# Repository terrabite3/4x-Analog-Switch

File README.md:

# 4x Analog Switch

This is a quad analog switch based on the [MAX333A](https://datasheets.maximintegrated.com/en/ds/MAX333A.pdf) analog switch IC. The jacks are *directly* connected to the switch IC for minimum resistance and maximum versatility. 

The switch may be used in either direction.

* Send two signals into the `A` and `B` ports, and select which one goes to the `X` port.
* Send a signal into the `X` port, and select whether it goes to the `A` or `B` port. The other port is pulled low with a 100k resistor.

The connection is selected by both the toggle switch and the `SEL` input. The toggle is a 3-position switch.

* When the switch is in the up position, `A` is selected.
* When the switch is in the down position, `B` is selected.
* When the switch is in the middle position, the `SEL` input selects `A` or `B`.
* If `SEL` is high (above 3V), `A` is selected. If `SEL` is low (below 2V), `B` is selected. The `SEL` input has a Schmitt trigger so that slowly changing inputs won't cause glitches.
* If the `SEL` input is unconnected and the switch is in the middle position, `B` is selected by default.

In addition to the standard 10-pin Eurorack power header, I've included two daisy-chain power headers at the top corners of the board. This will allow adjacent units to share power. I plan to add these to most of my new designs.

## BOM

Please see the [interactive BOM](https://htmlpreview.github.io/?https://github.com/terrabite3/4x-Analog-Switch/blob/main/bom/ibom.html) for full details. Most of the parts are super common and any established maker will have them in stock. The exception is the MAX333A itself, which is rather expensive -- $16 each at this time. I only used it because I already had them in my stash!

Note that the toggle switches must be SPDT **ON-OFF-ON** configuration!

### MAX4533 substitution

After designing this module, I learned of the [MAX4533](https://datasheets.maximintegrated.com/en/ds/MAX4533.pdf), which is pin compatible with the MAX333A. It features fault protection and is actually $4 cheaper at this writing. The only downside I see is somewhat higher on resistance. I recommend that you use this part instead.

## License

* You are free to build this design, modify it, and use parts of it in other designs.
* Most PCB fabs have a minimum order of 5 units. You may sell excess PCBs as bare PCBs, kits, or fully assembled modules. Just don't order extras with the intent of selling them.
* If you make substantial changes to the design, then you may treat the design as your own. For example, adding features, removing features, or changing the form factor. Changing the font on the panel and other superficial changes would not count.
* I urge you to release any derivative works under similar terms, but you don't have to.

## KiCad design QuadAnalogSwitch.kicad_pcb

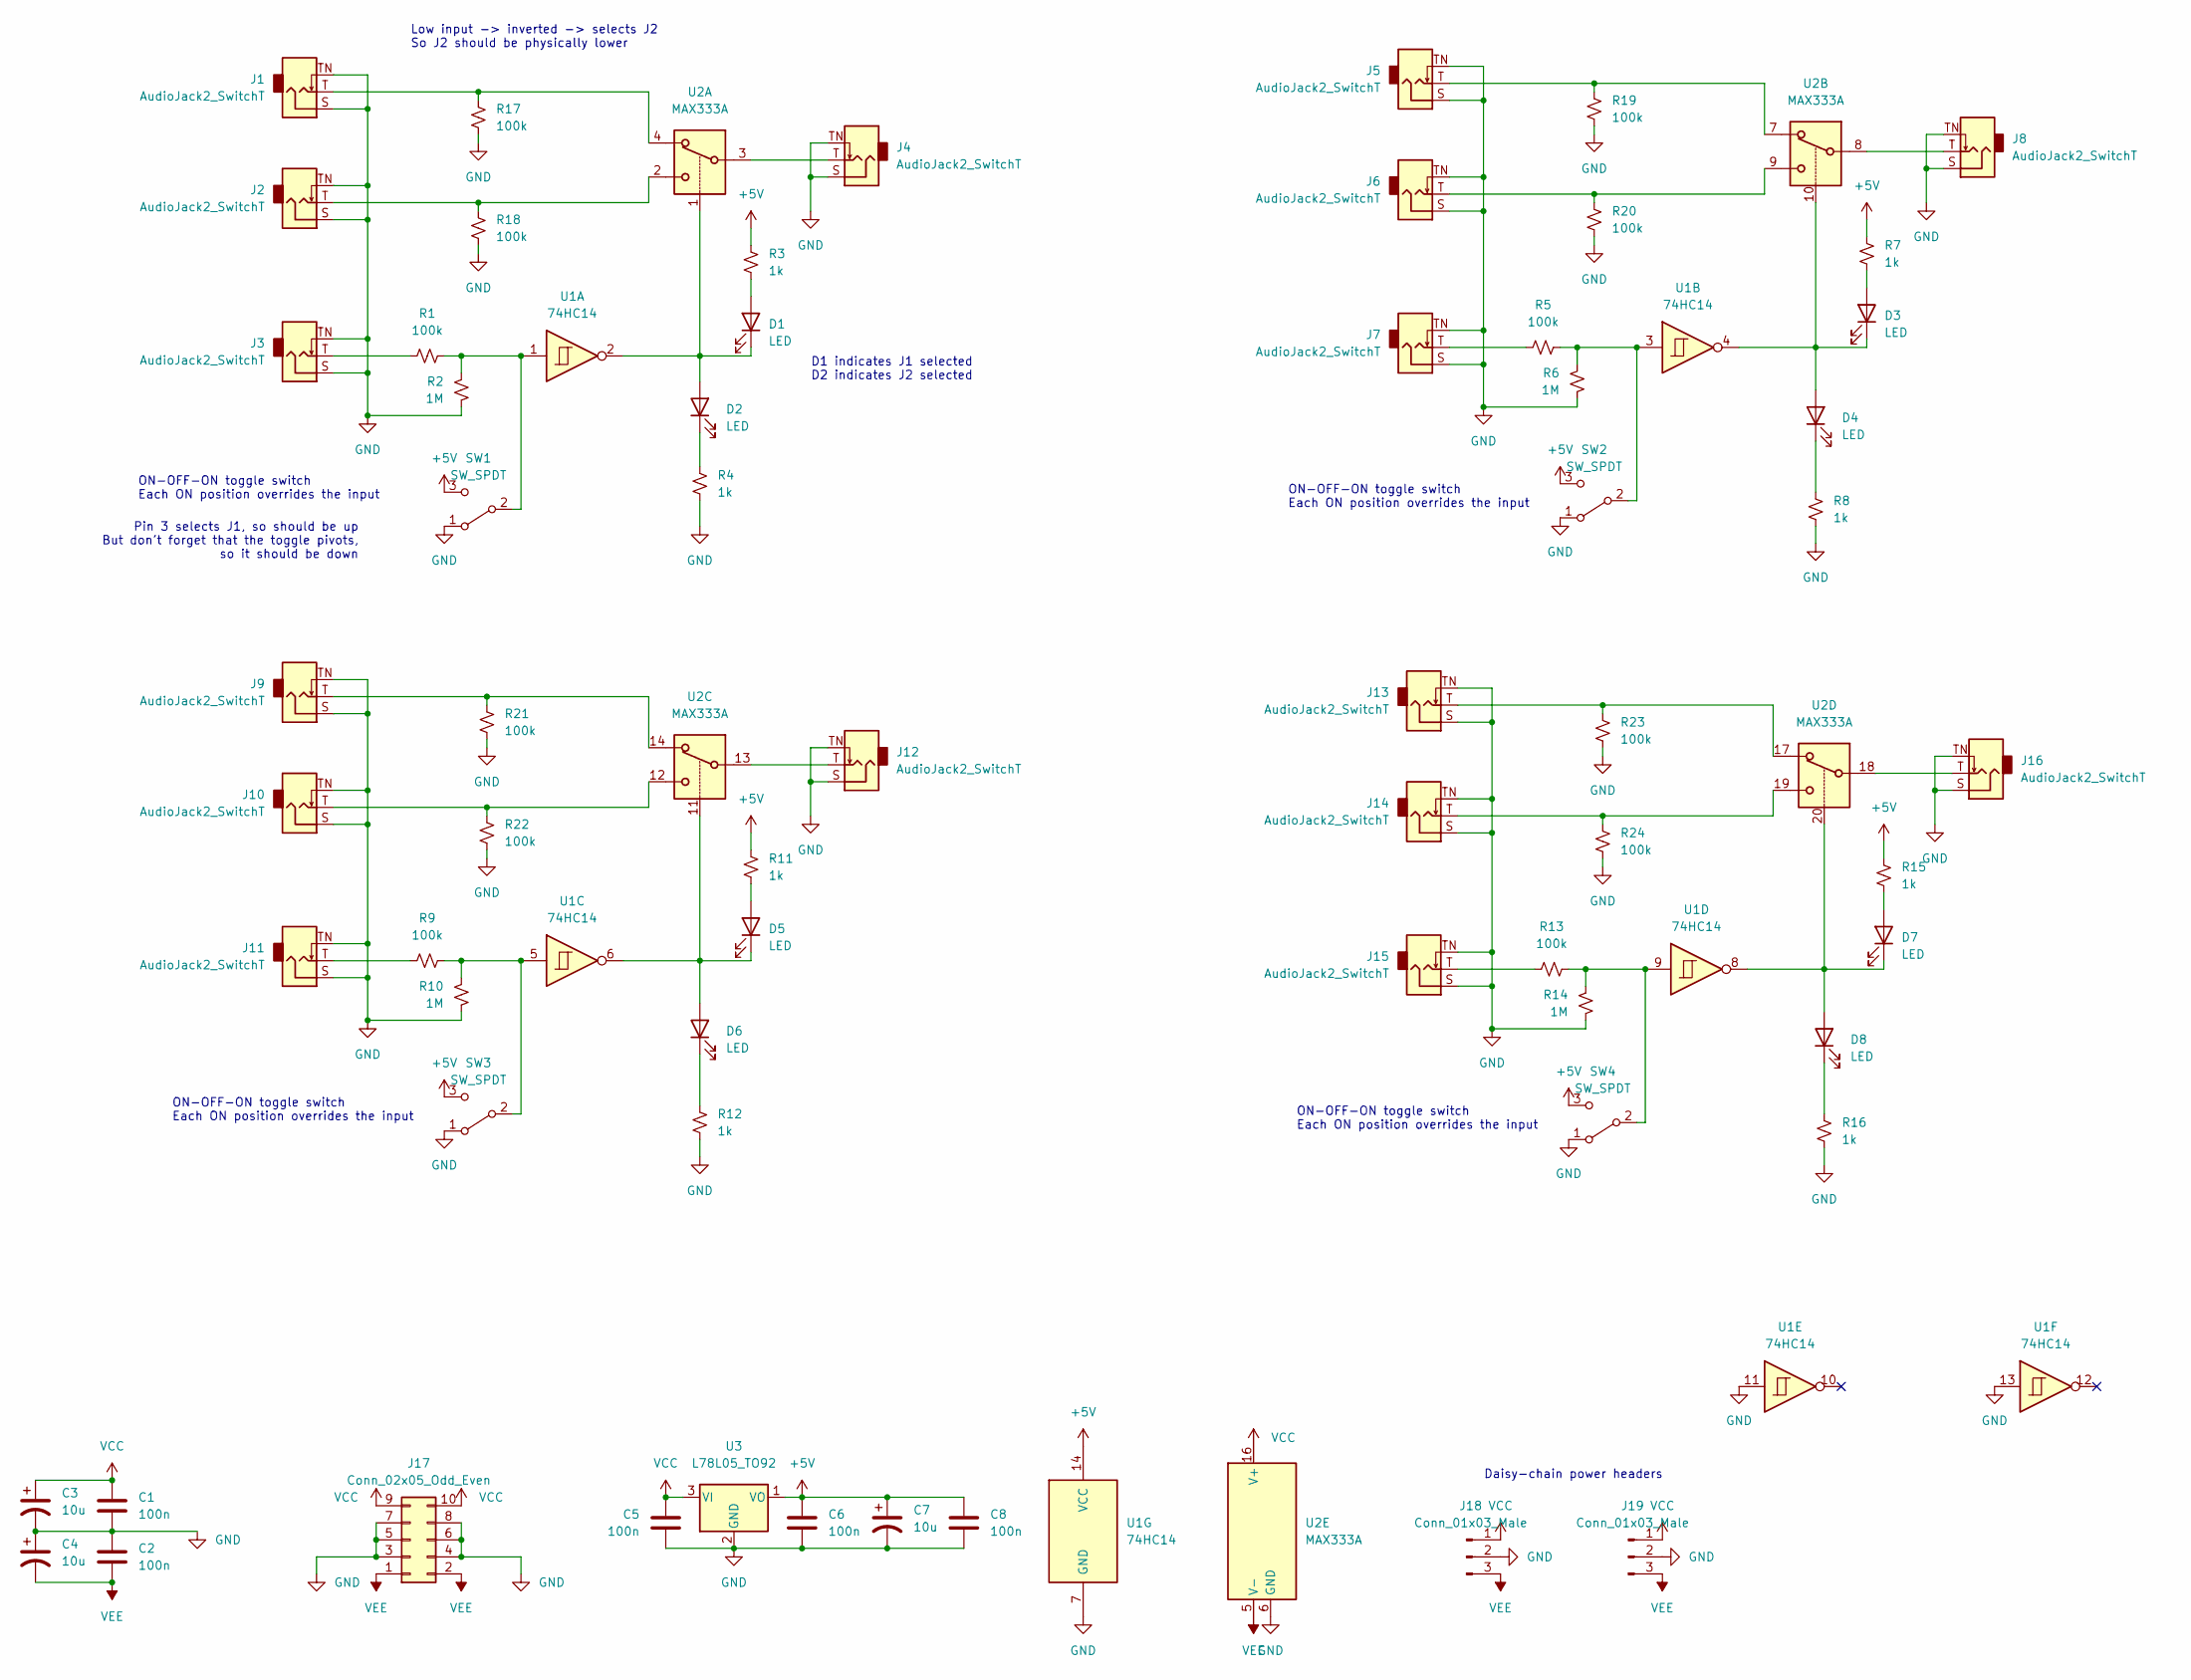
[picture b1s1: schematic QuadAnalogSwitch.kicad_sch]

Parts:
C1, C2, C5, C6, C8: 100n; C_Disc_D3.0mm_W1.6mm_P2.50mm
C3, C4, C7: 10u; CP_Radial_D5.0mm_P2.50mm
D1, D2, D3, D4, D5, D6, D7, D8: LED; LED_D3.0mm
J1, J2, J3, J4, J5, J6, J7, J8, J9, J10, J11, J12, J13, J14, J15, J16: AudioJack2_SwitchT; Jack_3.5mm_QingPu_WQP-PJ398SM_Stefan
J17: Conn_02x05_Odd_Even; IDC-Header_2x05_P2.54mm_Vertical
J18, J19: Conn_01x03_Male; PinHeader_1x03_P2.54mm_Vertical
R1, R5, R9, R13, R17, R18, R19, R20, R21, R22, R23, R24: 100k; R_Axial_DIN0204_L3.6mm_D1.6mm_P7.62mm_Horizontal
R2, R6, R10, R14: 1M; R_Axial_DIN0204_L3.6mm_D1.6mm_P7.62mm_Horizontal
R3, R4, R7, R8, R11, R12, R15, R16: 1k; R_Axial_DIN0204_L3.6mm_D1.6mm_P7.62mm_Horizontal
SW1, SW2, SW3, SW4: SW_SPDT; SW_MINI_TOGGLE
U1: 74HC14; DIP-14_W7.62mm
U2: MAX333A; DIP-20_W7.62mm
U3: L78L05_TO92; TO-92L_Inline_Wide

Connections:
+5V: C6.2, C7.1, C8.2, R3.2, R7.2, R11.2, R15.2, SW1.3 (C), SW2.3 (C), SW3.3 (C), SW4.3 (C), U1.14 (VCC), U3.1 (VO)
GND: C1.1, C2.2, C3.2, C4.1, C5.1, C6.1, C7.2, C8.1, J1.S, J1.TN, J2.S, J2.TN, J3.S, J3.TN, J4.S, J4.TN, J5.S, J5.TN, J6.S, J6.TN, J7.S, J7.TN, J8.S, J8.TN, J9.S, J9.TN, J10.S, J10.TN, J11.S, J11.TN, J12.S, J12.TN, J13.S, J13.TN, J14.S, J14.TN, J15.S, J15.TN, J16.S, J16.TN, J17.3, J17.4, J17.5, J17.6, J17.7, J17.8, J18.2, J19.2, R2.1, R4.1, R6.1, R8.1, R10.1, R12.1, R14.1, R16.1, R17.1, R18.1, R19.1, R20.1, R21.1, R22.1, R23.1, R24.1, SW1.1 (A), SW2.1 (A), SW3.1 (A), SW4.1 (A), U1.7 (GND), U1.11, U1.13, U2.6 (GND), U3.2 (GND)
unnamed: D1.1 (K), D2.2 (A), U1.2, U2.1
unnamed: D1.2 (A), R3.1
unnamed: D2.1 (K), R4.2
unnamed: D3.1 (K), D4.2 (A), U1.4, U2.10
unnamed: D3.2 (A), R7.1
unnamed: D4.1 (K), R8.2
unnamed: D5.1 (K), D6.2 (A), U1.6, U2.11
unnamed: D5.2 (A), R11.1
unnamed: D6.1 (K), R12.2
unnamed: D7.1 (K), D8.2 (A), U1.8, U2.20
unnamed: D7.2 (A), R15.1
unnamed: D8.1 (K), R16.2
unnamed: J1.T, R17.2, U2.4
unnamed: J2.T, R18.2, U2.2
unnamed: J3.T, R1.1
unnamed: J4.T, U2.3
unnamed: J5.T, R19.2, U2.7
unnamed: J6.T, R20.2, U2.9
unnamed: J7.T, R5.1
unnamed: J8.T, U2.8
unnamed: J9.T, R21.2, U2.14
unnamed: J10.T, R22.2, U2.12
unnamed: J11.T, R9.1
unnamed: J12.T, U2.13
unnamed: J13.T, R23.2, U2.17
unnamed: J14.T, R24.2, U2.19
unnamed: J15.T, R13.1
unnamed: J16.T, U2.18
unnamed: R1.2, R2.2, SW1.2 (B), U1.1
unnamed: R5.2, R6.2, SW2.2 (B), U1.3
unnamed: R9.2, R10.2, SW3.2 (B), U1.5
unnamed: R13.2, R14.2, SW4.2 (B), U1.9
VCC: C1.2, C3.1, C5.2, J17.9, J17.10, J18.1, J19.1, U2.16 (V+), U3.3 (VI)
VEE: C2.1, C4.2, J17.1, J17.2, J18.3, J19.3, U2.5 (V-)

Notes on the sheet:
D1 indicates J1 selected D2 indicates J2 selected
ON-OFF-ON toggle switch Each ON position overrides the input
Pin 3 selects J1, so should be up But don't forget that the toggle pivots, so it should be down
Low input -> inverted -> selects J2 So J2 should be physically lower
Daisy-chain power headers

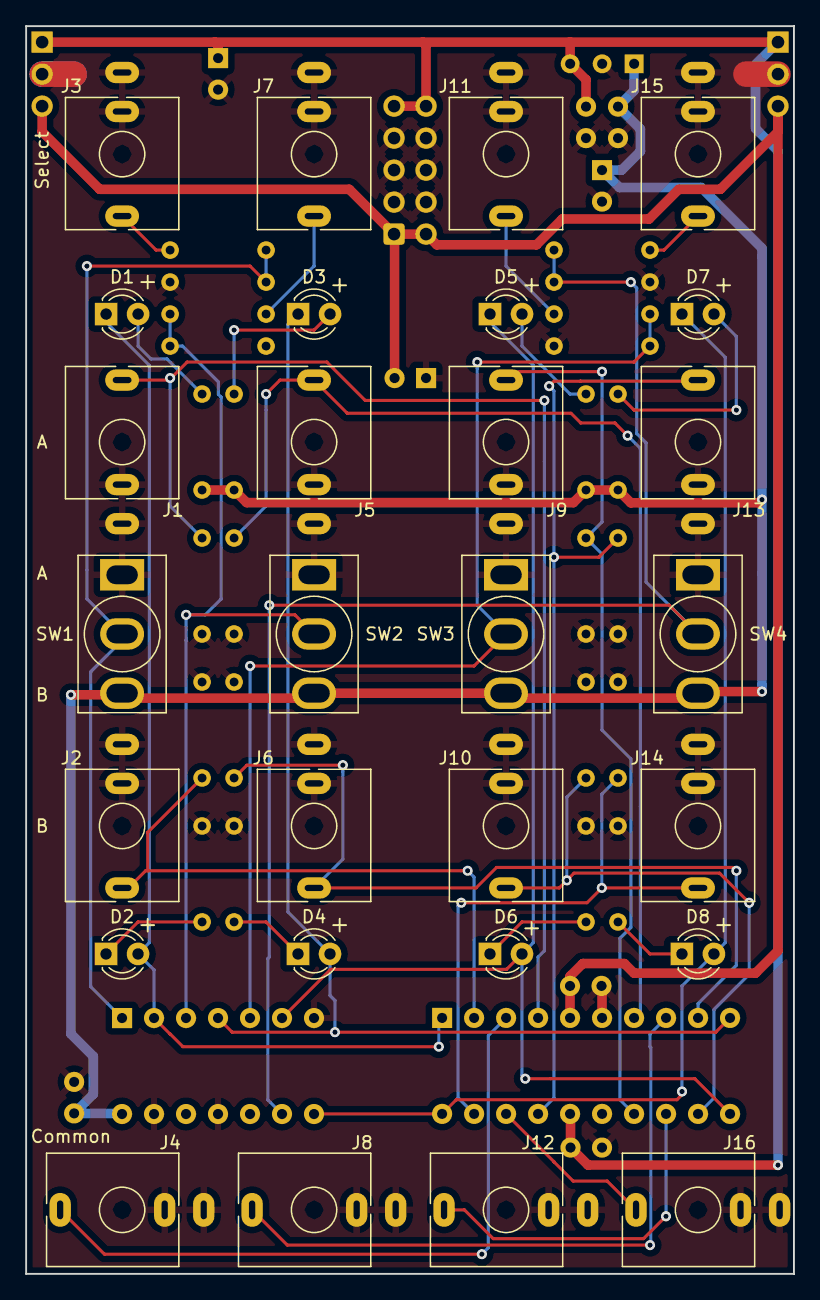
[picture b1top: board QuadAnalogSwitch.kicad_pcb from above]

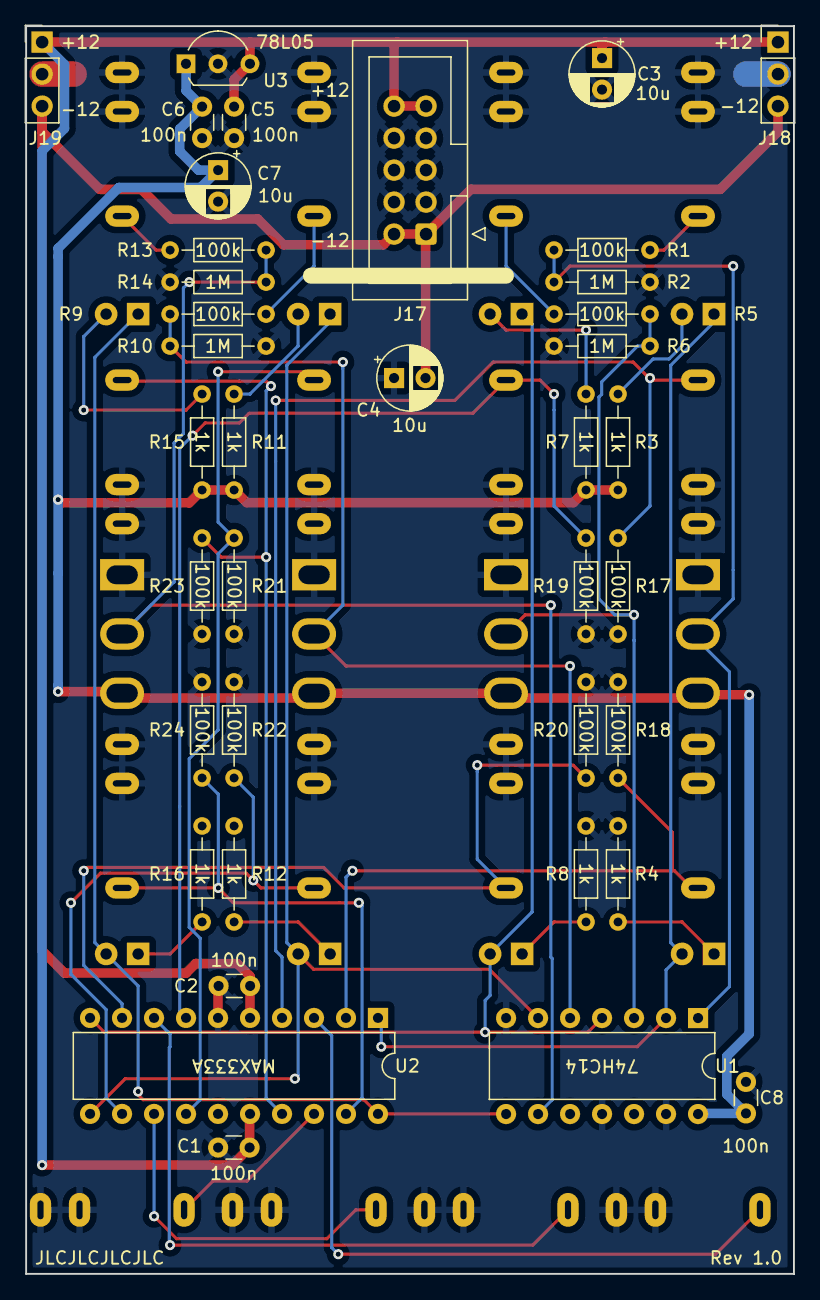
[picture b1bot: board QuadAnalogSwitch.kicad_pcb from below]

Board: 2 copper layers, 61.0 x 99.1 mm, 66 parts (38 on the bottom side), 36 nets.

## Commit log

2022-04-19 Change link to interactive BOM
2022-04-24 Add note about MAX4533
